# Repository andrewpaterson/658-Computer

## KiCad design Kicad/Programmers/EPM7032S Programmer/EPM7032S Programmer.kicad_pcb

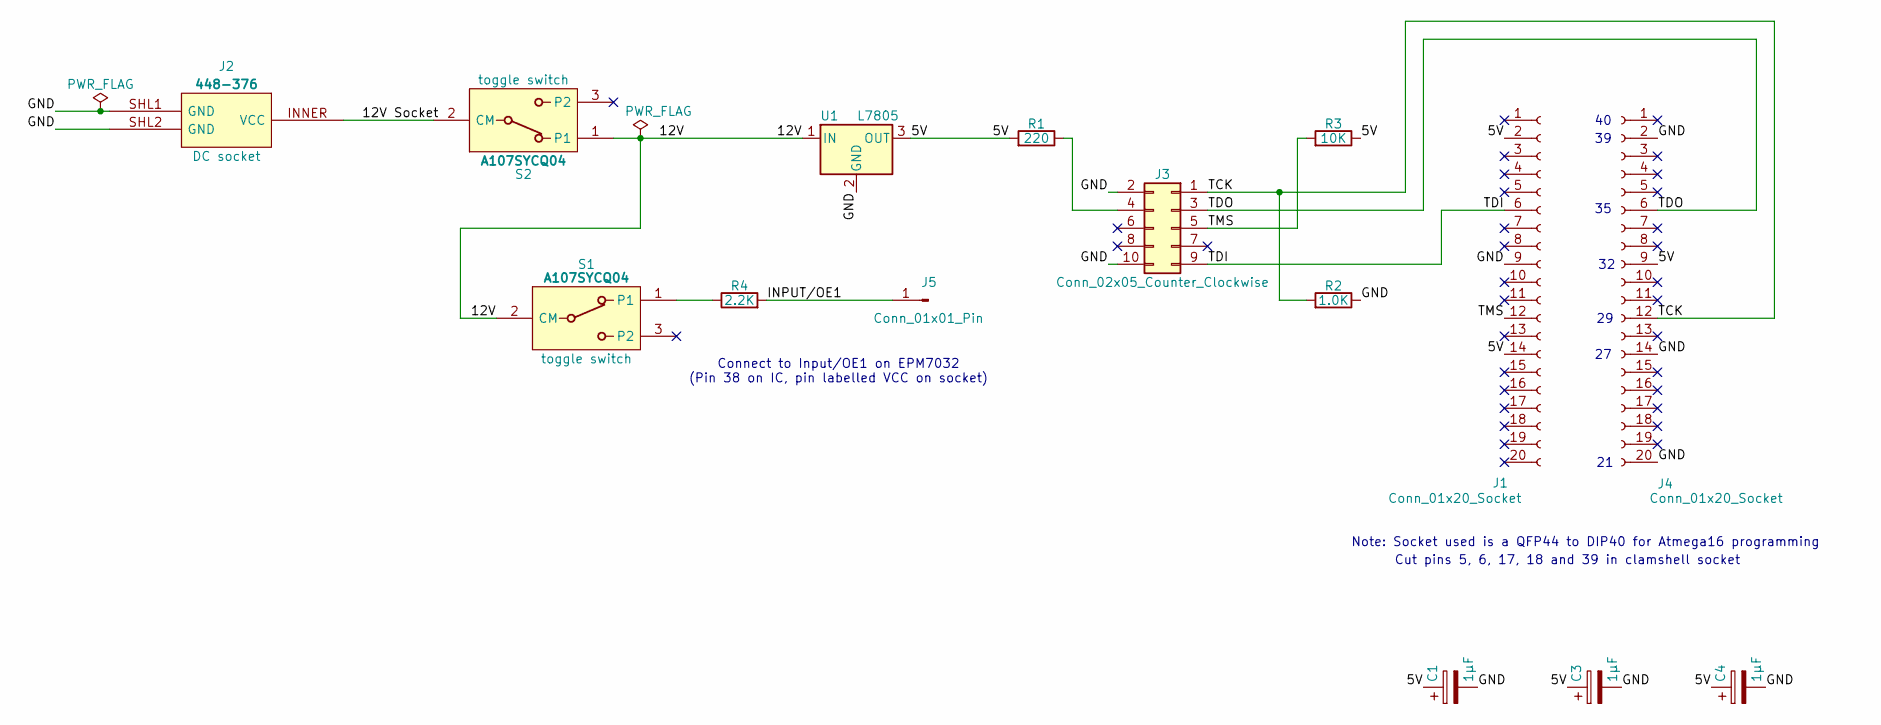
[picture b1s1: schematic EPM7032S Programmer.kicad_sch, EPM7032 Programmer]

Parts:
C1, C3, C4: 1μF; CP_Radial_D4.0mm_P2.00mm
J1, J4: Conn_01x20_Socket; PinSocket_1x20_P2.54mm_Vertical
J2: 448-376; 448376; Manufacturer_Part_Number 448-376
J3: Conn_02x05_Counter_Clockwise; PinHeader_2x05_P2.54mm_Vertical
J5: Conn_01x01_Pin; PinHeader_1x01_P2.54mm_Vertical
R1: 220; R_Axial_DIN0309_L9.0mm_D3.2mm_P12.70mm_Horizontal
R2: 1.0K; R_Axial_DIN0207_L6.3mm_D2.5mm_P7.62mm_Horizontal
R3: 10K; R_Axial_DIN0207_L6.3mm_D2.5mm_P7.62mm_Horizontal
R4: 2.2K; R_Axial_DIN0207_L6.3mm_D2.5mm_P7.62mm_Horizontal
S1, S2: A107SYCQ04; Manufacturer_Part_Number A107SYCQ04; Mouser Part Number 506-5-1825137-1
U1: L7805; TO-220-3_Vertical

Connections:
/5V: C1.1, C3.1, C4.1, J1.2, J1.14, J4.9, R1.2, R3.1, U1.3 (OUT)
/12V: S1.2 (CM), S2.1, U1.1 (IN)
/12V Socket: J2.INNER (VCC), S2.2 (CM)
/GND: C1.2, C3.2, C4.2, J1.9, J2.SHL1 (GND), J2.SHL2 (GND), J3.2, J3.10, J4.2, J4.14, J4.20, R2.1, U1.2 (GND)
/INPUT/OE1: J5.1, R4.2
/TCK: J3.1, J4.12, R2.2
/TDI: J1.6, J3.9
/TDO: J3.3, J4.6
/TMS: J1.12, J3.5, R3.2
unnamed: J3.4, R1.1
unnamed: R4.1, S1.1

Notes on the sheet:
Note: Socket used is a QFP44 to DIP40 for Atmega16 programming
Connect to Input/OE1 on EPM7032 (Pin 38 on IC, pin labelled VCC on socket)
Cut pins 5, 6, 17, 18 and 39 in clamshell socket

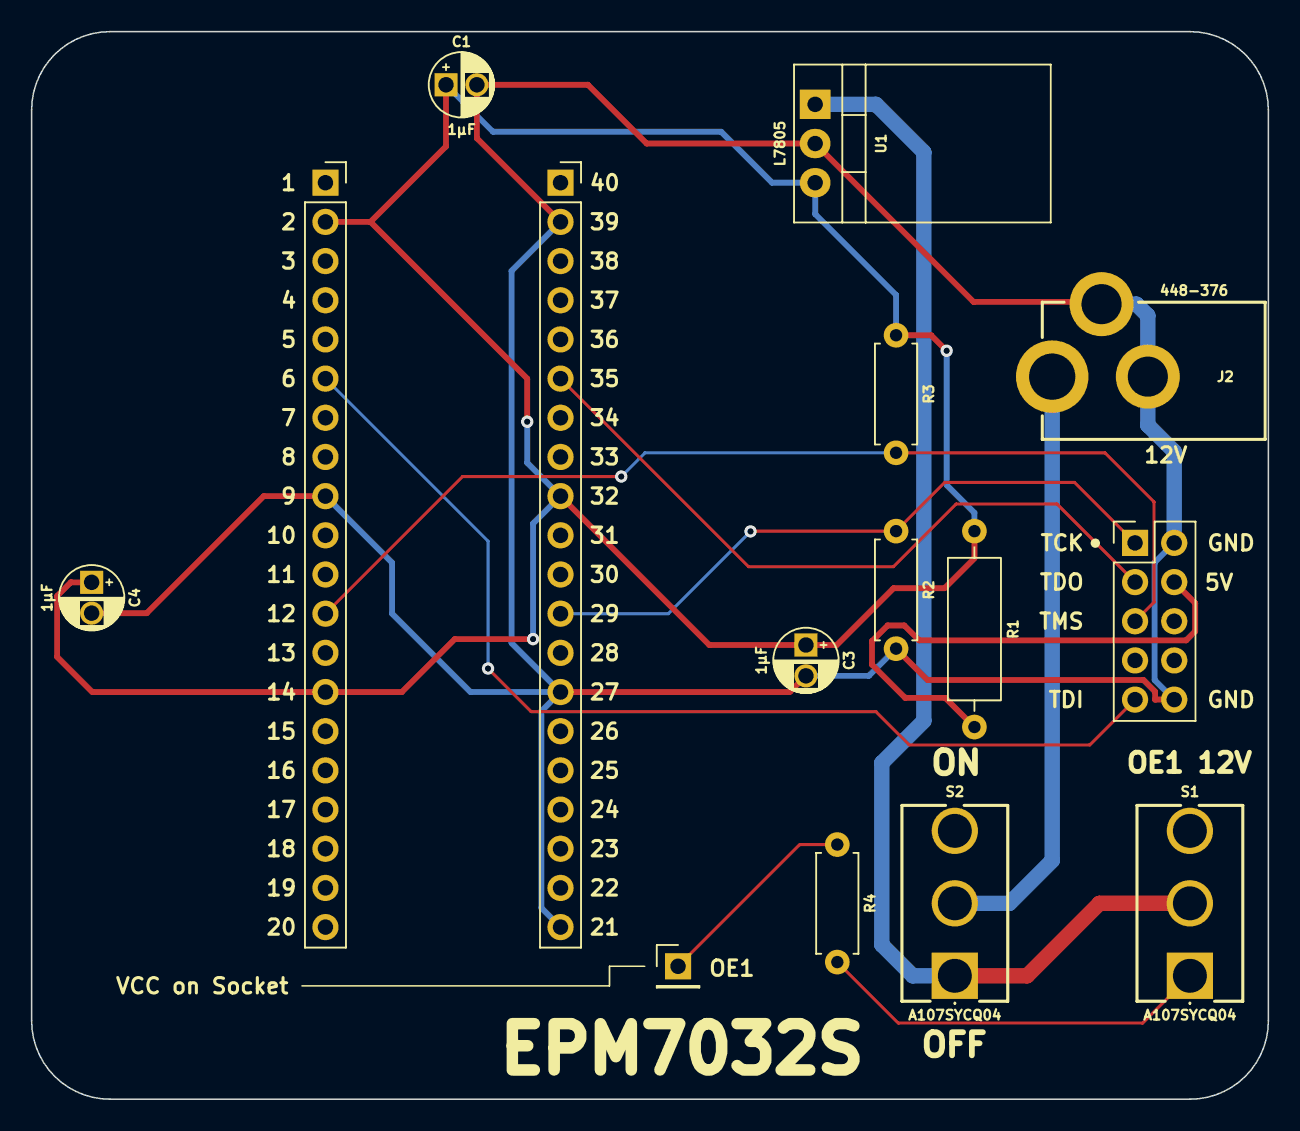
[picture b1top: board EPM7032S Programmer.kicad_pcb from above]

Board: 2 copper layers, 80.2 x 69.2 mm, 15 parts (0 on the bottom side), 11 nets.

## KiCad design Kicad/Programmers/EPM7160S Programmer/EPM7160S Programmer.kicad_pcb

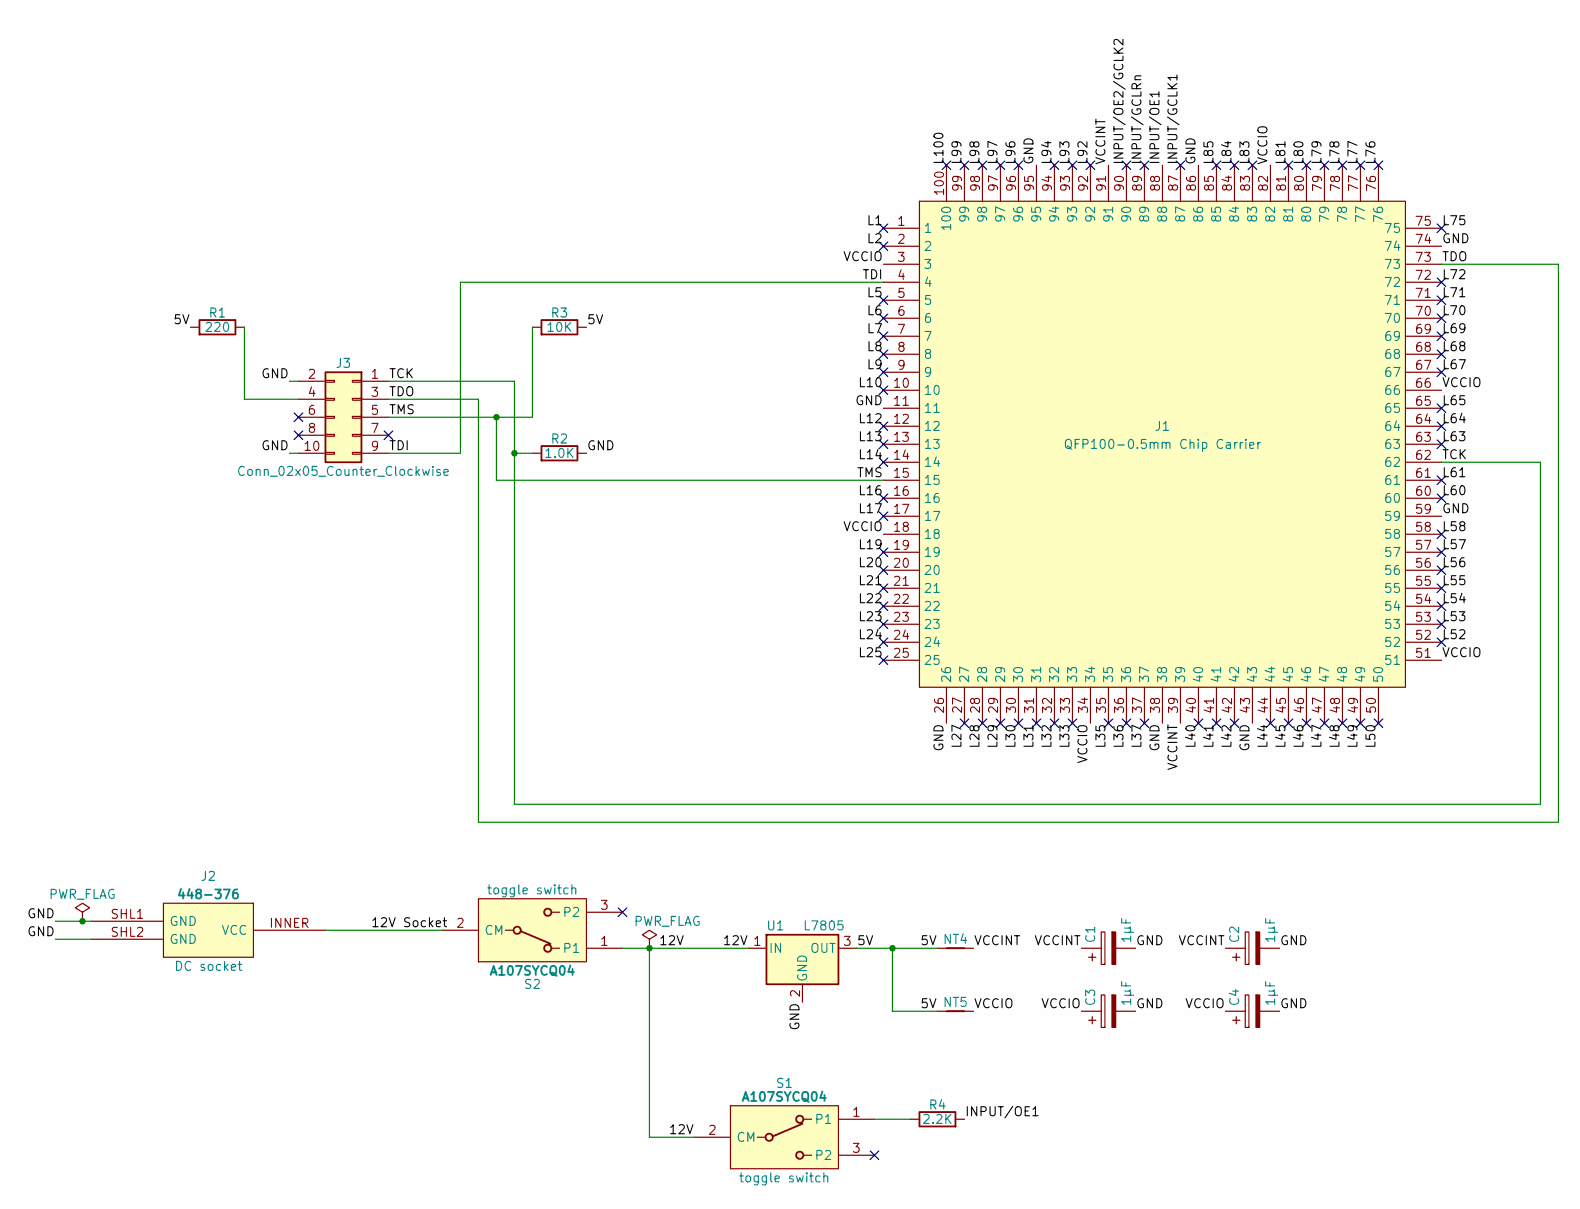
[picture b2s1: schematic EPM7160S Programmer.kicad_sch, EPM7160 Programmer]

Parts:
C1, C2, C3, C4: 1μF; CP_Radial_D4.0mm_P2.00mm
J1: AllSocket-QFP-100-14X14-0.5-Clamshell
J2: 448-376; 448376; Manufacturer_Part_Number 448-376
J3: Conn_02x05_Counter_Clockwise; PinHeader_2x05_P2.54mm_Vertical
NT4, NT5: NetTie_2; NetTie-2_SMD_Pad0.5mm
R1: 220; R_Axial_DIN0309_L9.0mm_D3.2mm_P12.70mm_Horizontal
R2: 1.0K; R_Axial_DIN0207_L6.3mm_D2.5mm_P7.62mm_Horizontal
R3: 10K; R_Axial_DIN0207_L6.3mm_D2.5mm_P7.62mm_Horizontal
R4: 2.2K; R_Axial_DIN0207_L6.3mm_D2.5mm_P7.62mm_Horizontal
S1, S2: A107SYCQ04; Manufacturer_Part_Number A107SYCQ04; Mouser Part Number 506-5-1825137-1
U1: L7805; TO-220-3_Vertical

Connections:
/5V: NT4.1, NT5.1, R1.2, R3.1, U1.3 (OUT)
/12V: S1.2 (CM), S2.1, U1.1 (IN)
/12V Socket: J2.INNER (VCC), S2.2 (CM)
/GND: C1.2, C2.2, C3.2, C4.2, J1.11, J1.26, J1.38, J1.43, J1.59, J1.74, J1.86, J1.95, J2.SHL1 (GND), J2.SHL2 (GND), J3.2, J3.10, R2.1, U1.2 (GND)
/INPUT/GCLK1: J1.87
/INPUT/GCLRn: J1.89
/INPUT/OE1: J1.88, R4.2
/INPUT/OE2/GCLK2: J1.90
/L1: J1.1
/L2: J1.2
/L5: J1.5
/L6: J1.6
/L7: J1.7
/L8: J1.8
/L9: J1.9
/L10: J1.10
/L12: J1.12
/L13: J1.13
/L14: J1.14
/L16: J1.16
/L17: J1.17
/L19: J1.19
/L20: J1.20
/L21: J1.21
/L22: J1.22
/L23: J1.23
/L24: J1.24
/L25: J1.25
/L27: J1.27
/L28: J1.28
/L29: J1.29
/L30: J1.30
/L31: J1.31
/L32: J1.32
/L33: J1.33
/L35: J1.35
/L36: J1.36
/L37: J1.37
/L40: J1.40
/L41: J1.41
/L42: J1.42
/L44: J1.44
/L45: J1.45
/L46: J1.46
/L47: J1.47
/L48: J1.48
/L49: J1.49
/L50: J1.50
/L52: J1.52
/L53: J1.53
/L54: J1.54
/L55: J1.55
/L56: J1.56
/L57: J1.57
/L58: J1.58
/L60: J1.60
/L61: J1.61
/L63: J1.63
/L64: J1.64
/L65: J1.65
/L67: J1.67
/L68: J1.68
/L69: J1.69
/L70: J1.70
/L71: J1.71
/L72: J1.72
/L75: J1.75
/L76: J1.76
/L77: J1.77
/L78: J1.78
/L79: J1.79
/L80: J1.80
/L81: J1.81
/L83: J1.83
/L84: J1.84
/L85: J1.85
/L92: J1.92
/L93: J1.93
/L94: J1.94
/L96: J1.96
/L97: J1.97
/L98: J1.98
/L99: J1.99
/L100: J1.100
/TCK: J1.62, J3.1, R2.2
/TDI: J1.4, J3.9
/TDO: J1.73, J3.3
/TMS: J1.15, J3.5, R3.2
/VCCINT: C1.1, C2.1, J1.39, J1.91, NT4.2
/VCCIO: C3.1, C4.1, J1.3, J1.18, J1.34, J1.51, J1.66, J1.82, NT5.2
unnamed: J3.4, R1.1
unnamed: R4.1, S1.1

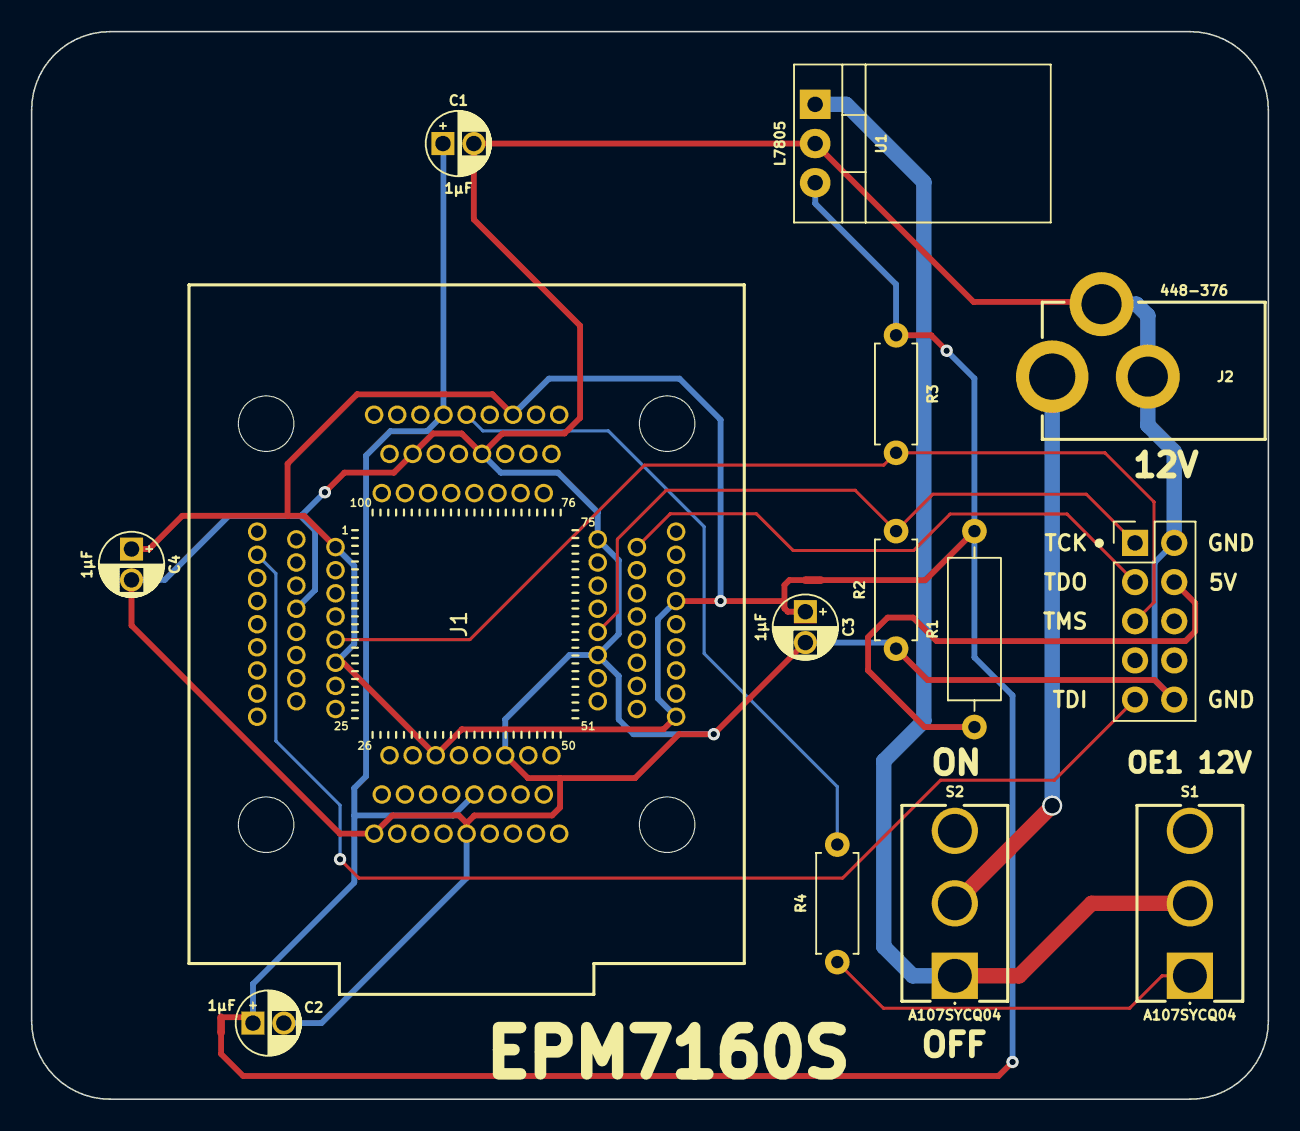
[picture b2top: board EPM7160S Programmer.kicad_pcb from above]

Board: 2 copper layers, 80.2 x 69.2 mm, 16 parts (0 on the bottom side), 13 nets.

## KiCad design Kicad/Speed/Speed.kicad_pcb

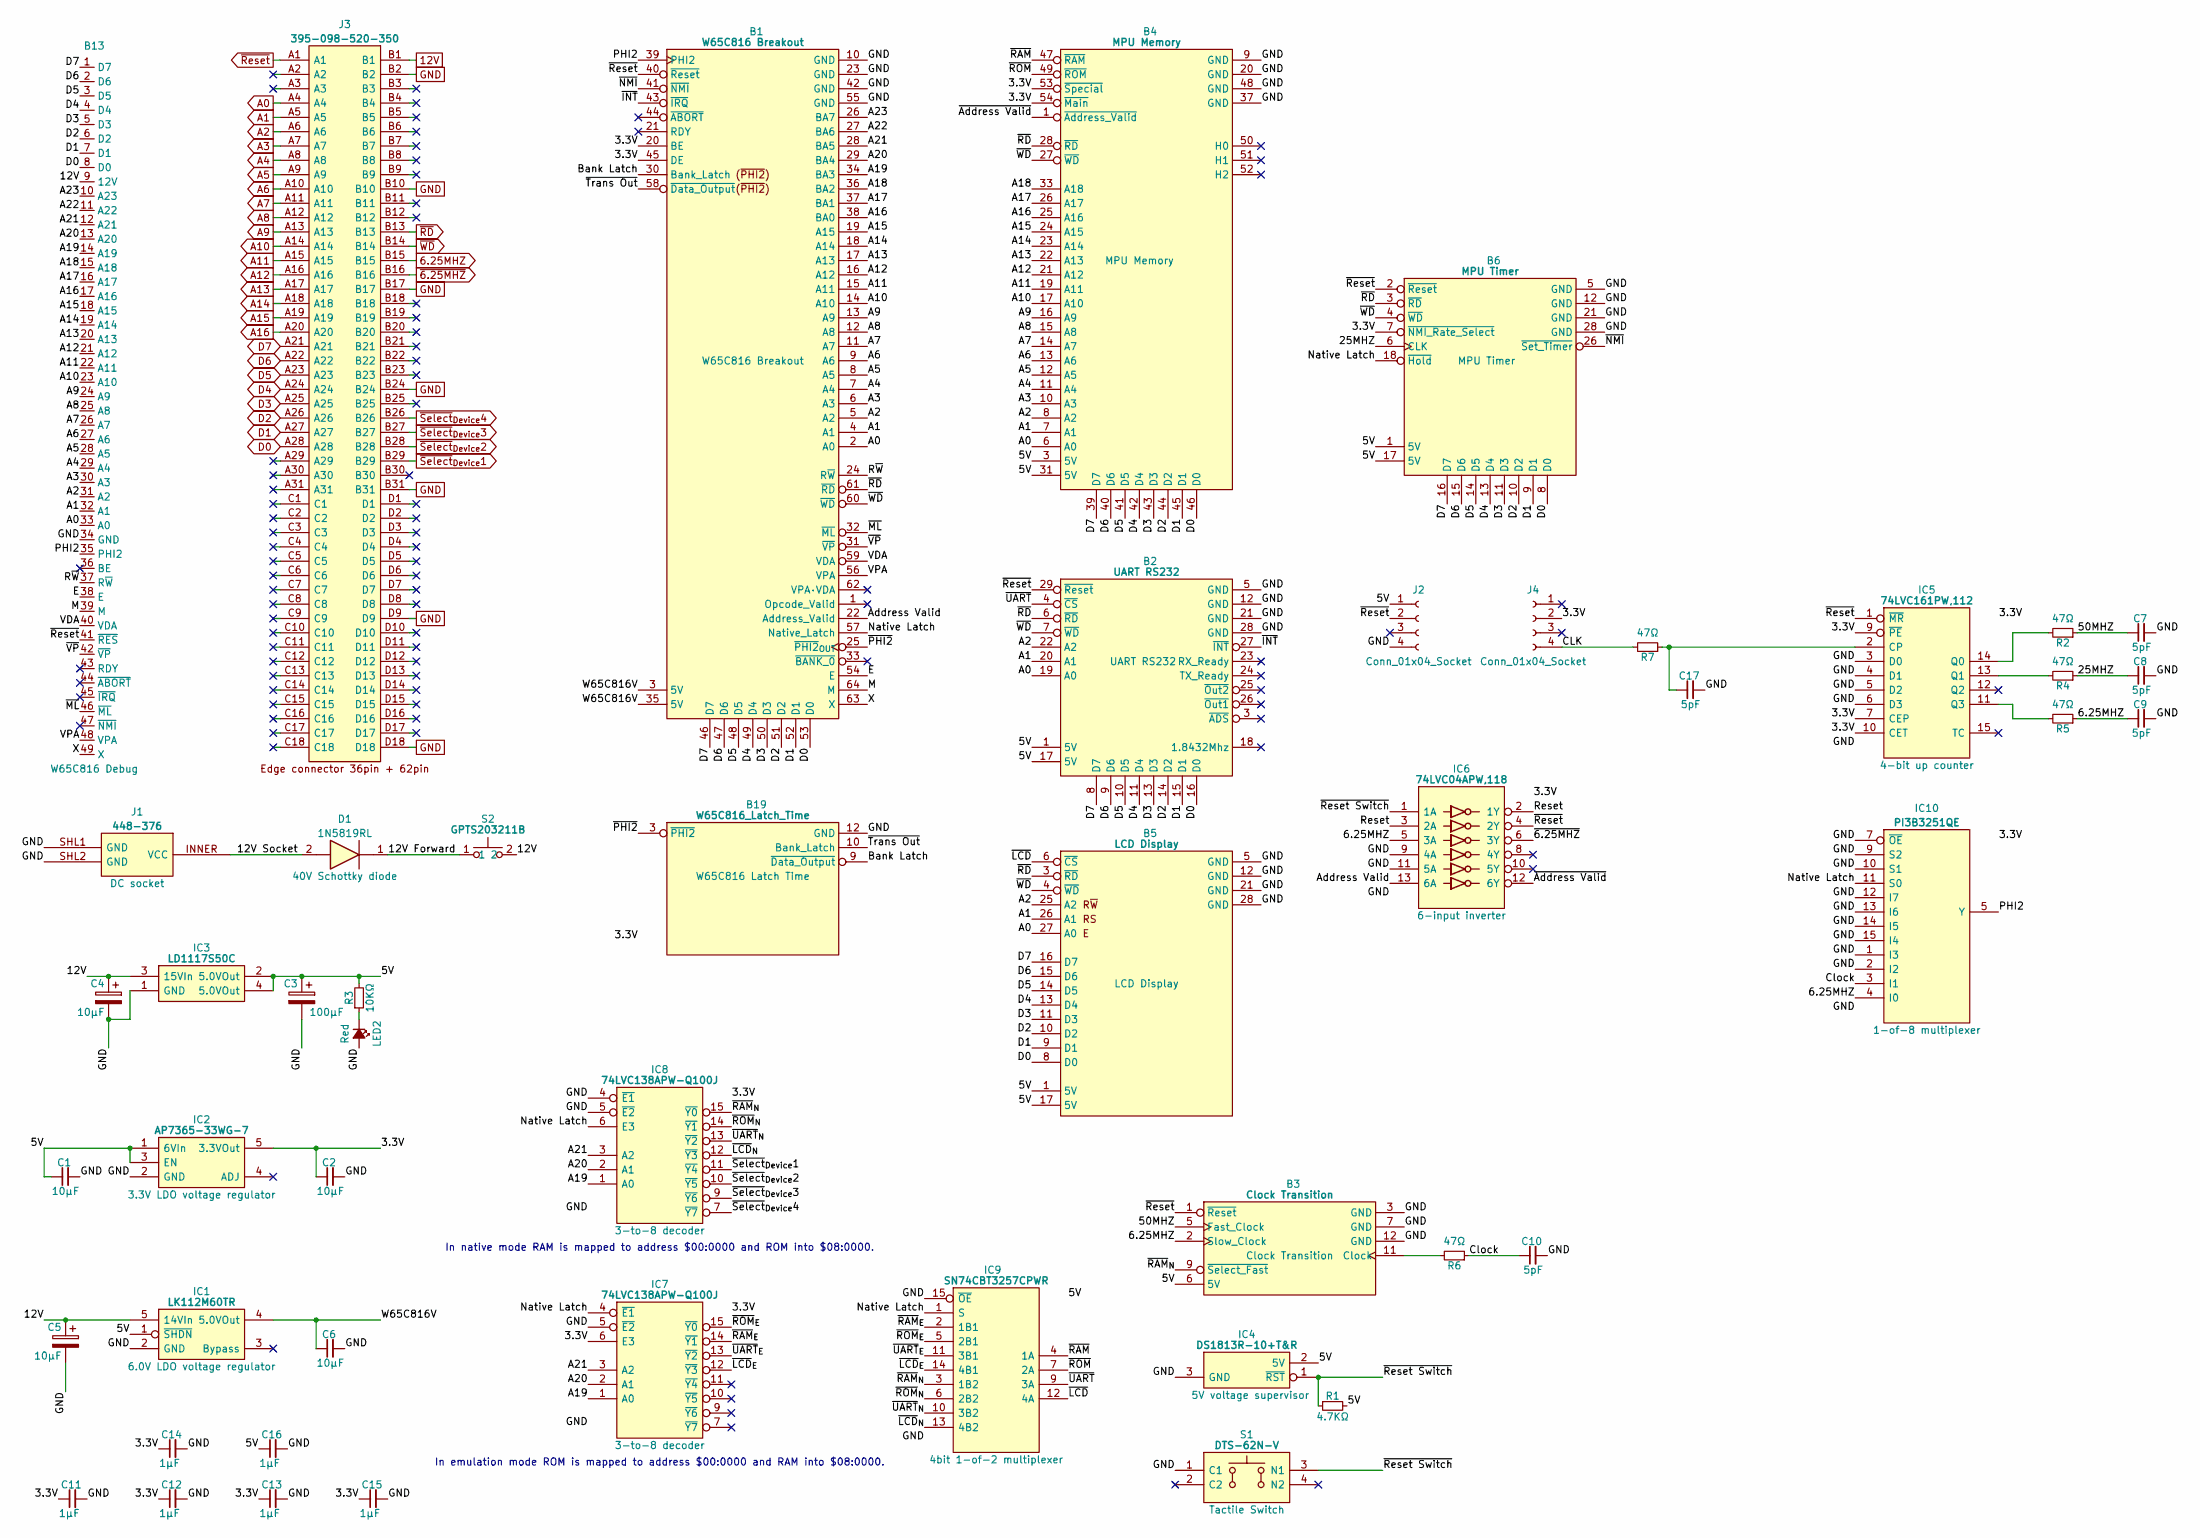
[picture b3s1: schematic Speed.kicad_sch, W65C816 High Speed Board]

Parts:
B1: W65C816 Breakout; HCP65_W65C816_Breakout
B2: UART RS232; HCP65_RS232_UART
B3: Clock Transition; HCP65_Clock_Transition
B4: MPU Memory; HCP65_MPU_Memory
B5: LCD Display; HCP65_LCD_Display
B6: MPU Timer; HCP65_MPU_Timer
B13: W65C816 Debug; HCP65_W65C816_Debug_Display
B19: W65C816_Latch_Time; HCP65_W65C816_Latch_Time
C1, C2, C6: 10µF; C_0805
C3: 100μF; CP_Radial_D4.0mm_P2.00mm
C4, C5: 10μF; CP_Radial_D4.0mm_P2.00mm
C7, C8, C9, C10, C17: 5pF; C_0805
C11, C12, C13, C14, C15, C16: 1µF; C_0805
D1: 1N5819RL; DIOAD1414W86L464D238; Manufacturer_Part_Number 1N5819RL; Mouser Part Number 511-1N5819-TR
IC1: LK112M60TR; SOT95P285X130-5N; Manufacturer_Part_Number LK112M60TR
IC2: AP7365-33WG-7; SOT95P285X130-5N; Manufacturer_Part_Number AP7365-33WG-7; Mouser Part Number 621-AP7365-33WG-7
IC3: LD1117S50C; LD1117S33C; Manufacturer_Part_Number LD1117S50C
IC4: DS1813R-10+T&R; SOT95P237X112-3N; Mouser Part Number 700-DS1813R-10T&R
IC5: 74LVC161PW,112; SOP65P640X110-16N; Mouser Part Number 771-LVC161PW112
IC6: 74LVC04APW,118; SOP65P640X110-14N; Manufacturer_Part_Number 74LVC04APW,118; Mouser Part Number 771-74LVC04APW-T
IC7, IC8: 74LVC138APW-Q100J; SOP65P640X110-16N; Mouser Part Number 771-74LVC138APWQ100J
IC9: SN74CBT3257CPWR; SOP65P640X120-16N; Manufacturer_Part_Number SN74CBT3257CPWR; Mouser Part Number 595-SN74CBT3257CPWR
IC10: PI3B3251QE; SOP64P599X175-16N; Manufacturer_Part_Number PI3B3251QE; Mouser Part Number 729-PI3B3251QE
J1: 448-376; 448376; Manufacturer_Part_Number 448-376
J2, J4: Conn_01x04_Socket; PinSocket_1x04_P2.54mm_Vertical
J3: 395-098-520-350; 98pin Edge Connector; Manufacturer_Part_Number 395-098-520-350; Mouser Part Number 587-395-098-520-350
LED2: Red; LED_D5.0mm
R1: 4.7KΩ; R_0805
R2, R4, R5, R6, R7: 47Ω; R_0805
R3: 10KΩ; R_0805
S1: DTS-62N-V; DTS62NV; Manufacturer_Part_Number DTS-62N-V; Mouser Part Number 113-DTS-62N-V
S2: GPTS203211B; Manufacturer_Part_Number GPTS203211B; Mouser Part Number 629-GPTS203211B

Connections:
6.25MHZ: B3.2 (Slow_Clock), C9.1, IC6.5 (3A), IC10.4 (I0), J3.B15, R5.1
12V: B13.9 (12V), C4.1, C5.1, IC1.5 (14VIn), IC3.3 (15VIn), J3.B1, S2.2
/3.3V: B1.20 (BE), B1.45 (DE), B4.53 (~Special), B4.54 (~Main), B6.7 (~NMI_Rate_Select), B19.6 (3.3V), C2.1, C11.1, C12.1, C13.1, C14.1, C15.1, IC2.5 (3.3VOut), IC5.7 (CEP), IC5.9 (~PE), IC5.10 (CET), IC5.16 (3V), IC6.14 (3V), IC7.6 (E3), IC7.16 (3V), IC8.16 (3V), IC10.16 (3V), J4.2
/5V: B2.1 (5V), B2.17 (5V), B3.6 (5V), B4.3 (5V), B4.31 (5V), B5.1 (5V), B5.17 (5V), B6.1 (5V), B6.17 (5V), C1.1, C3.1, C16.1, IC1.1 (~SHDN), IC2.1 (6VIn), IC2.3 (EN), IC3.2 (5.0VOut), IC3.4 (5.0VOut), IC4.2 (5V), IC9.16 (5V), J2.1, R1.2, R3.2
/12V Forward: D1.1, S2.1
/12V Socket: D1.2, J1.INNER (VCC)
/25MHZ: B6.6 (CLK), C8.1, R4.1
/50MHZ: B3.5 (Fast_Clock), C7.1, R2.1
/A17: B1.37 (BA1), B4.26 (A17), B13.16 (A17)
/A18: B1.36 (BA2), B4.33 (A18), B13.15 (A18)
/A19: B1.34 (BA3), B13.14 (A19), IC7.1 (A0), IC8.1 (A0)
/A20: B1.29 (BA4), B13.13 (A20), IC7.2 (A1), IC8.2 (A1)
/A21: B1.28 (BA5), B13.12 (A21), IC7.3 (A2), IC8.3 (A2)
/A22: B1.27 (BA6), B13.11 (A22)
/A23: B1.26 (BA7), B13.10 (A23)
/Address Valid: B1.22 (Address_Valid), IC6.13 (6A)
/Bank Latch: B1.30 (Bank_Latch), B19.9 (~Data_Output)
/CLK: J4.4, R7.2
/Clock: C10.1, IC10.3 (I1), R6.1
/E: B1.54 (E), B13.38 (E)
/M: B1.64 (M), B13.39 (M)
/Native Latch: B1.57 (Native_Latch), B6.18 (~Hold), IC7.4 (~E1), IC8.6 (E3), IC9.1 (S), IC10.11 (S0)
/PHI2: B1.39 (PHI2), B13.35 (PHI2), IC10.5 (Y)
/Reset: IC6.2 (1Y), IC6.3 (2A)
/R~W: B1.24 (R~W), B13.37 (R~W)
/VDA: B1.59 (VDA), B13.40 (VDA)
/VPA: B1.56 (VPA), B13.48 (VPA)
/W65C816V: B1.3 (5V), B1.35 (5V), C6.1, IC1.4 (5.0VOut)
/X: B1.63 (X), B13.49 (X)
/~Address Valid: B4.1 (~Address_Valid), IC6.12 (6Y)
/~INT: B1.43 (~IRQ), B2.27 (~INT)
/~LCD: B5.6 (~CS), IC9.12 (4A)
/~LCD_{E}: IC7.12 (~Y3), IC9.14 (4B1)
/~LCD_{N}: IC8.12 (~Y3), IC9.13 (4B2)
/~ML: B1.32 (~ML), B13.46 (~ML)
/~NMI: B1.41 (~NMI), B6.26 (~Set_Timer)
/~PHI2: B1.25 (~PHI2_{OUT}), B19.3 (~PHI2)
/~RAM: B4.47 (~RAM), IC9.4 (1A)
/~RAM_{E}: IC7.14 (~Y1), IC9.2 (1B1)
/~RAM_{N}: B3.9 (~Select_Fast), IC8.15 (~Y0), IC9.3 (1B2)
/~ROM: B4.49 (~ROM), IC9.7 (2A)
/~ROM_{E}: IC7.15 (~Y0), IC9.5 (2B1)
/~ROM_{N}: IC8.14 (~Y1), IC9.6 (2B2)
/~Reset Switch: IC4.1 (~RST), IC6.1 (1A), R1.1, S1.3 (N1)
/~Trans Out: B1.58 (~Data_Output), B19.10 (Bank_Latch)
/~UART: B2.4 (~CS), IC9.9 (3A)
/~UART_{E}: IC7.13 (~Y2), IC9.11 (3B1)
/~UART_{N}: IC8.13 (~Y2), IC9.10 (3B2)
/~VP: B1.31 (~VP), B13.42 (~VP)
A0: B1.2 (A0), B2.19 (A0), B4.6 (A0), B5.27 (A0), B13.33 (A0), J3.A4
A1: B1.4 (A1), B2.20 (A1), B4.7 (A1), B5.26 (A1), B13.32 (A1), J3.A5
A2: B1.5 (A2), B2.22 (A2), B4.8 (A2), B5.25 (A2), B13.31 (A2), J3.A6
A3: B1.6 (A3), B4.10 (A3), B13.30 (A3), J3.A7
A4: B1.7 (A4), B4.11 (A4), B13.29 (A4), J3.A8
A5: B1.8 (A5), B4.12 (A5), B13.28 (A5), J3.A9
A6: B1.9 (A6), B4.13 (A6), B13.27 (A6), J3.A10
A7: B1.11 (A7), B4.14 (A7), B13.26 (A7), J3.A11
A8: B1.12 (A8), B4.15 (A8), B13.25 (A8), J3.A12
A9: B1.13 (A9), B4.16 (A9), B13.24 (A9), J3.A13
A10: B1.14 (A10), B4.17 (A10), B13.23 (A10), J3.A14
A11: B1.15 (A11), B4.19 (A11), B13.22 (A11), J3.A15
A12: B1.16 (A12), B4.21 (A12), B13.21 (A12), J3.A16
A13: B1.17 (A13), B4.22 (A13), B13.20 (A13), J3.A17
A14: B1.18 (A14), B4.23 (A14), B13.19 (A14), J3.A18
A15: B1.19 (A15), B4.24 (A15), B13.18 (A15), J3.A19
A16: B1.38 (BA0), B4.25 (A16), B13.17 (A16), J3.A20
D0: B1.53 (D0), B2.16 (D0), B4.46 (D0), B5.8 (D0), B6.8 (D0), B13.8 (D0), J3.A28
D1: B1.52 (D1), B2.15 (D1), B4.45 (D1), B5.9 (D1), B6.9 (D1), B13.7 (D1), J3.A27
D2: B1.51 (D2), B2.14 (D2), B4.44 (D2), B5.10 (D2), B6.10 (D2), B13.6 (D2), J3.A26
D3: B1.50 (D3), B2.13 (D3), B4.43 (D3), B5.11 (D3), B6.11 (D3), B13.5 (D3), J3.A25
D4: B1.49 (D4), B2.11 (D4), B4.42 (D4), B5.13 (D4), B6.13 (D4), B13.4 (D4), J3.A24
D5: B1.48 (D5), B2.10 (D5), B4.41 (D5), B5.14 (D5), B6.14 (D5), B13.3 (D5), J3.A23
D6: B1.47 (D6), B2.9 (D6), B4.40 (D6), B5.15 (D6), B6.15 (D6), B13.2 (D6), J3.A22
D7: B1.46 (D7), B2.8 (D7), B4.39 (D7), B5.16 (D7), B6.16 (D7), B13.1 (D7), J3.A21
GND: B1.10 (GND), B1.23 (GND), B1.42 (GND), B1.55 (GND), B2.5 (GND), B2.12 (GND), B2.21 (GND), B2.28 (GND), B3.3 (GND), B3.7 (GND), B3.12 (GND), B4.9 (GND), B4.20 (GND), B4.37 (GND), B4.48 (GND), B5.5 (GND), B5.12 (GND), B5.21 (GND), B5.28 (GND), B6.5 (GND), B6.12 (GND), B6.21 (GND), B6.28 (GND), B13.34 (GND), B19.12 (GND), C1.2, C2.2, C3.2, C4.2, C5.2, C6.2, C7.2, C8.2, C9.2, C10.2, C11.2, C12.2, C13.2, C14.2, C15.2, C16.2, C17.2, IC1.2 (GND), IC2.2 (GND), IC3.1 (GND), IC4.3 (GND), IC5.3 (D0), IC5.4 (D1), IC5.5 (D2), IC5.6 (D3), IC5.8 (GND), IC6.7 (GND), IC6.9 (4A), IC6.11 (5A), IC7.5 (~E2), IC7.8 (GND), IC8.4 (~E1), IC8.5 (~E2), IC8.8 (GND), IC9.8 (GND), IC9.15 (~OE), IC10.1 (I3), IC10.2 (I2), IC10.7 (~OE), IC10.8 (GND), IC10.9 (S2), IC10.10 (S1), IC10.12 (I7), IC10.13 (I6), IC10.14 (I5), IC10.15 (I4), J1.SHL1 (GND), J1.SHL2 (GND), J2.4, J3.B2, J3.B10, J3.B17, J3.B24, J3.B31, J3.D9, J3.D18, LED2.2 (A), S1.1 (C1)
unnamed: B3.11 (Clock), R6.2
unnamed: C17.1, IC5.2 (CP), R7.1
unnamed: IC5.14 (Q0), R2.2
unnamed: IC5.13 (Q1), R4.2
unnamed: IC5.11 (Q3), R5.2
unnamed: LED2.1 (K), R3.1
~6.25MHZ: IC6.6 (3Y), J3.B16
~RD: B1.61 (~RD), B2.6 (~RD), B4.28 (~RD), B5.3 (~RD), B6.3 (~RD), J3.B13
~Reset: B1.40 (~Reset), B2.29 (~Reset), B3.1 (~Reset), B6.2 (~Reset), B13.41 (~RES), IC5.1 (~MR), IC6.4 (2Y), J2.2, J3.A1
~Select_{Device}1: IC8.11 (~Y4), J3.B29
~Select_{Device}2: IC8.10 (~Y5), J3.B28
~Select_{Device}3: IC8.9 (~Y6), J3.B27
~Select_{Device}4: IC8.7 (~Y7), J3.B26
~WD: B1.60 (~WD), B2.7 (~WD), B4.27 (~WD), B5.4 (~WD), B6.4 (~WD), J3.B14

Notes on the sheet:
In emulation mode ROM is mapped to address $00:0000 and RAM into $08:0000.
In native mode RAM is mapped to address $00:0000 and ROM into $08:0000.

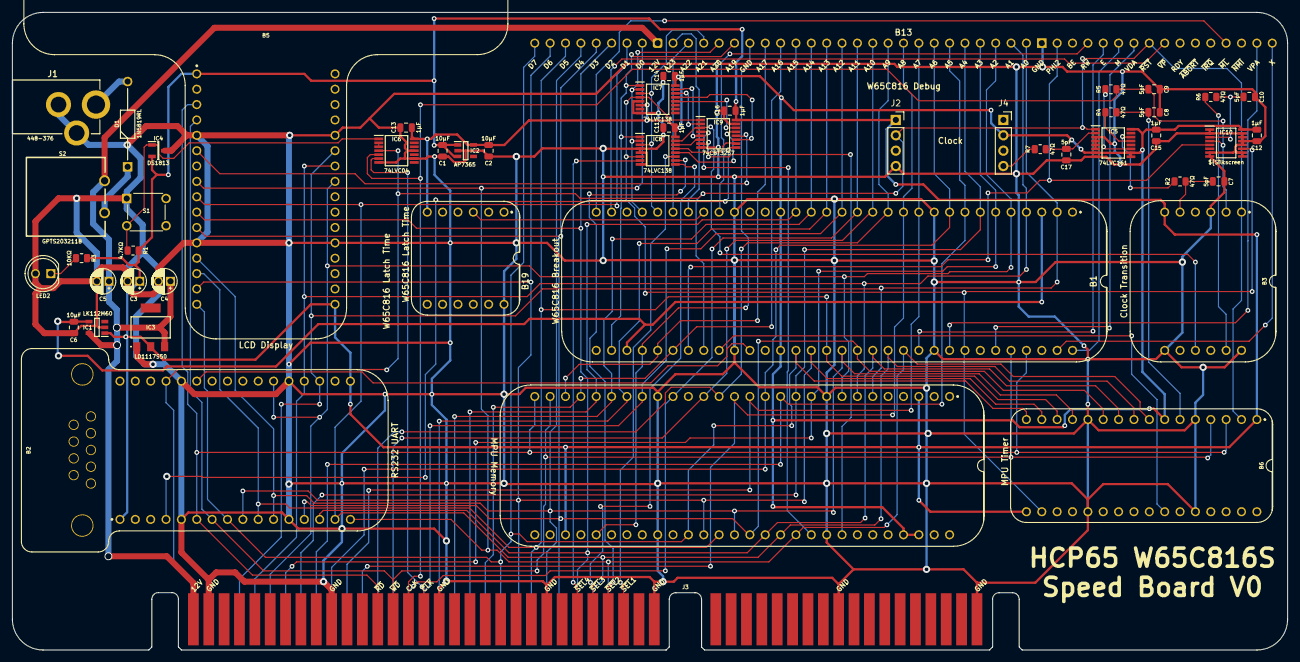
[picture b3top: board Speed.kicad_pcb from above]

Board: 2 copper layers, 210.8 x 105.4 mm, 50 parts (0 on the bottom side), 89 nets.

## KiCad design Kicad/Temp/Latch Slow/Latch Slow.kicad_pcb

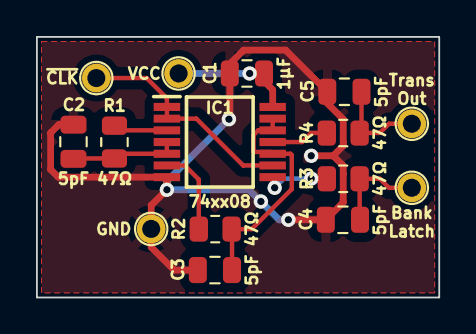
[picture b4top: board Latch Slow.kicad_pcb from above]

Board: 2 copper layers, 22.4 x 14.5 mm, 15 parts (0 on the bottom side), 11 nets.

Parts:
C1: 1μF; C_0805
C2, C3, C4, C5: 5pF; C_0805
IC1: SN74AHCT08PWRG4; SOP65P640X110-14N
J1, J2, J3, J4, J5: Conn_01x01_Pin; Plated_Hole_D1.0mm
R1, R2, R3, R4: 47Ω; R_0805

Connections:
/5V: C1.1, IC1.14 (3V), J1.1
/Bank Latch: C4.1, J4.1, R3.1
/GND: C1.2, C2.2, C3.2, C4.2, C5.2, IC1.7 (GND), J2.1
/~PHI2: IC1.1 (1A), IC1.2 (1B), IC1.9 (3A), J3.1
/~PHI2_{2}: C2.1, IC1.4 (2A), IC1.5 (2B), R1.1
/~PHI2_{3}: C3.1, IC1.10 (3B), IC1.12 (4A), IC1.13 (4B), R2.1
/~Trans Out: C5.1, J5.1, R4.1
unnamed: IC1.3 (1Y), R1.2
unnamed: IC1.6 (2Y), R2.2
unnamed: IC1.8 (3Y), R3.2
unnamed: IC1.11 (4Y), R4.2

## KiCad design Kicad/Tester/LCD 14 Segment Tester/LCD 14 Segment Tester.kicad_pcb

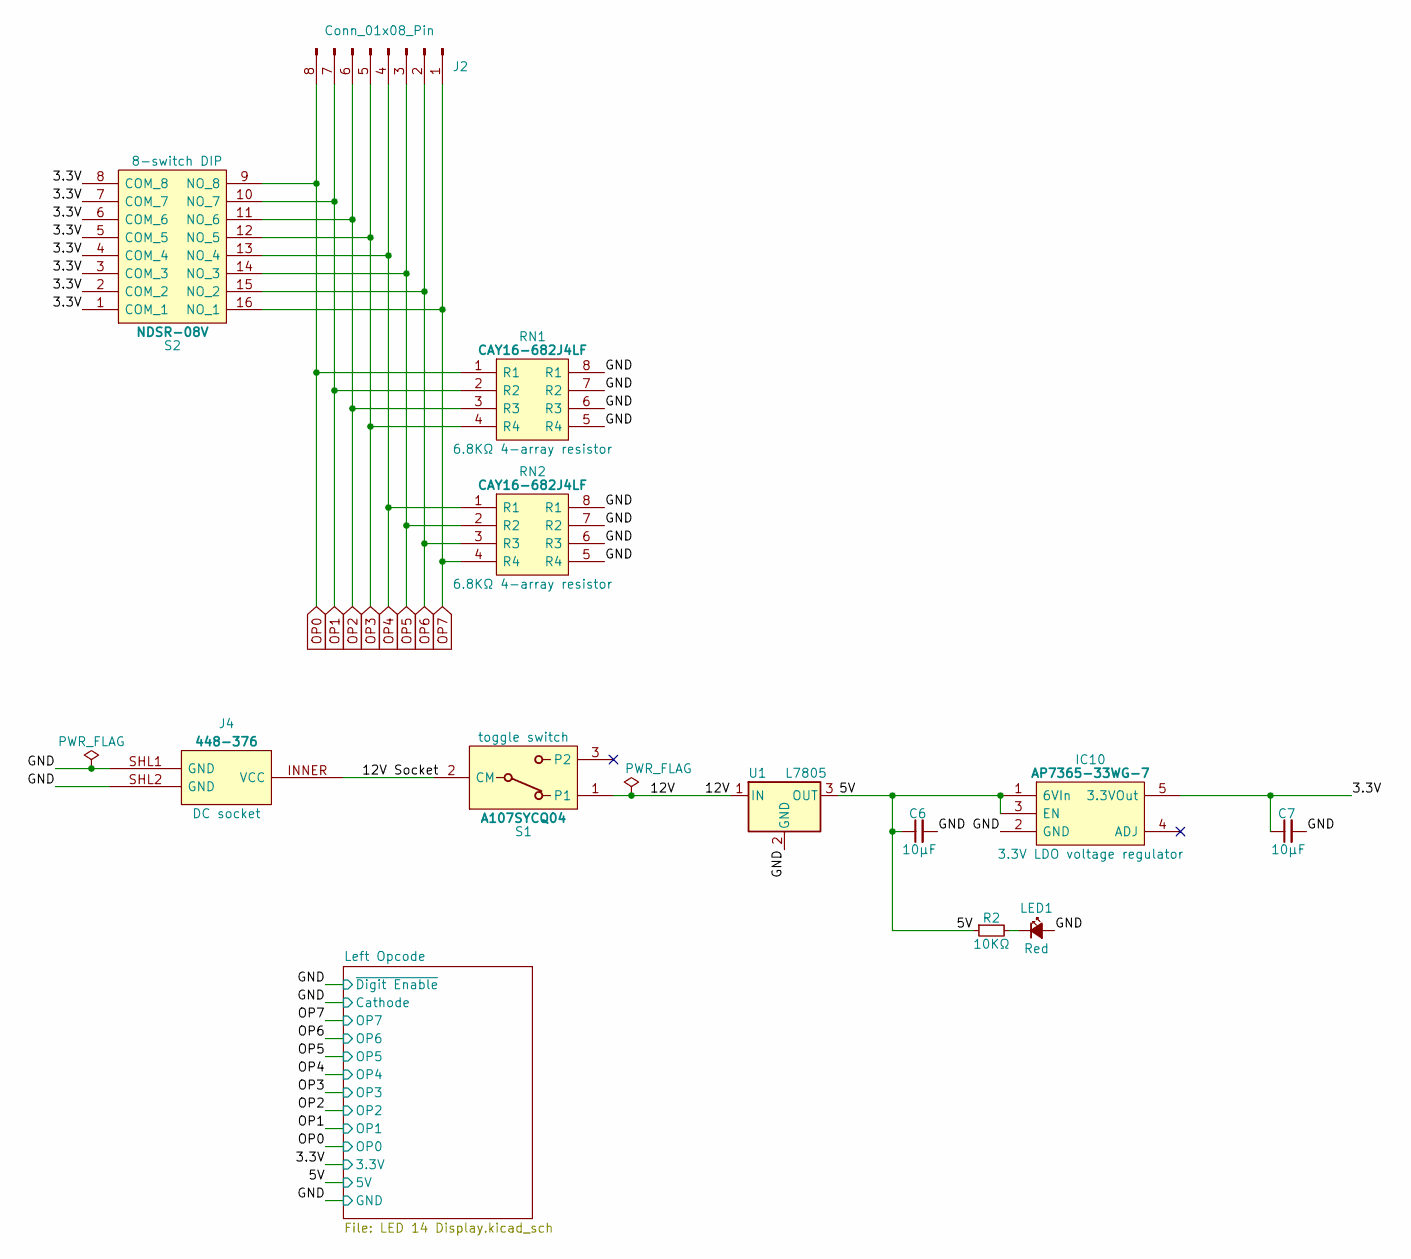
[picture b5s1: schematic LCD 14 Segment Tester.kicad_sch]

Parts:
C6, C7: 10µF; C_0805
IC10: AP7365-33WG-7; SOT95P285X130-5N; Manufacturer_Part_Number AP7365-33WG-7; Mouser Part Number 621-AP7365-33WG-7
J2: Conn_01x08_Pin; PinHeader_1x08_P2.54mm_Vertical
J4: 448-376; 448376; Manufacturer_Part_Number 448-376
LED1: Red; LED_D5.0mm
R2: 10KΩ; R_0805
RN1, RN2: CAY16-682J4LF; CAY16-J4
S1: A107SYCQ04; Manufacturer_Part_Number A107SYCQ04; Mouser Part Number 506-5-1825137-1
S2: NDSR-08V; DIPS762W77P254L2168H585Q16N; Manufacturer_Part_Number NDSR-08-V
U1: L7805; TO-220-3_Vertical

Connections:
/3.3V: C7.1, IC10.5 (3.3VOut), S2.1 (COM_1), S2.2 (COM_2), S2.3 (COM_3), S2.4 (COM_4), S2.5 (COM_5), S2.6 (COM_6), S2.7 (COM_7), S2.8 (COM_8); also elsewhere on the board
/5V: C6.1, IC10.1 (6VIn), IC10.3 (EN), R2.1, U1.3 (OUT); also elsewhere on the board
/12V: S1.1, U1.1 (IN)
/12V Socket: J4.INNER (VCC), S1.2 (CM)
/GND: C6.2, C7.2, IC10.2 (GND), J4.SHL1 (GND), J4.SHL2 (GND), LED1.2 (A), RN1.5 (R4), RN1.6 (R3), RN1.7 (R2), RN1.8 (R1), RN2.5 (R4), RN2.6 (R3), RN2.7 (R2), RN2.8 (R1), U1.2 (GND); also elsewhere on the board
unnamed: LED1.1 (K), R2.2
OP0: J2.8, RN1.1 (R1), S2.9 (NO_8); also elsewhere on the board
OP1: J2.7, RN1.2 (R2), S2.10 (NO_7); also elsewhere on the board
OP2: J2.6, RN1.3 (R3), S2.11 (NO_6); also elsewhere on the board
OP3: J2.5, RN1.4 (R4), S2.12 (NO_5); also elsewhere on the board
OP4: J2.4, RN2.1 (R1), S2.13 (NO_4); also elsewhere on the board
OP5: J2.3, RN2.2 (R2), S2.14 (NO_3); also elsewhere on the board
OP6: J2.2, RN2.3 (R3), S2.15 (NO_2); also elsewhere on the board
OP7: J2.1, RN2.4 (R4), S2.16 (NO_1); also elsewhere on the board
